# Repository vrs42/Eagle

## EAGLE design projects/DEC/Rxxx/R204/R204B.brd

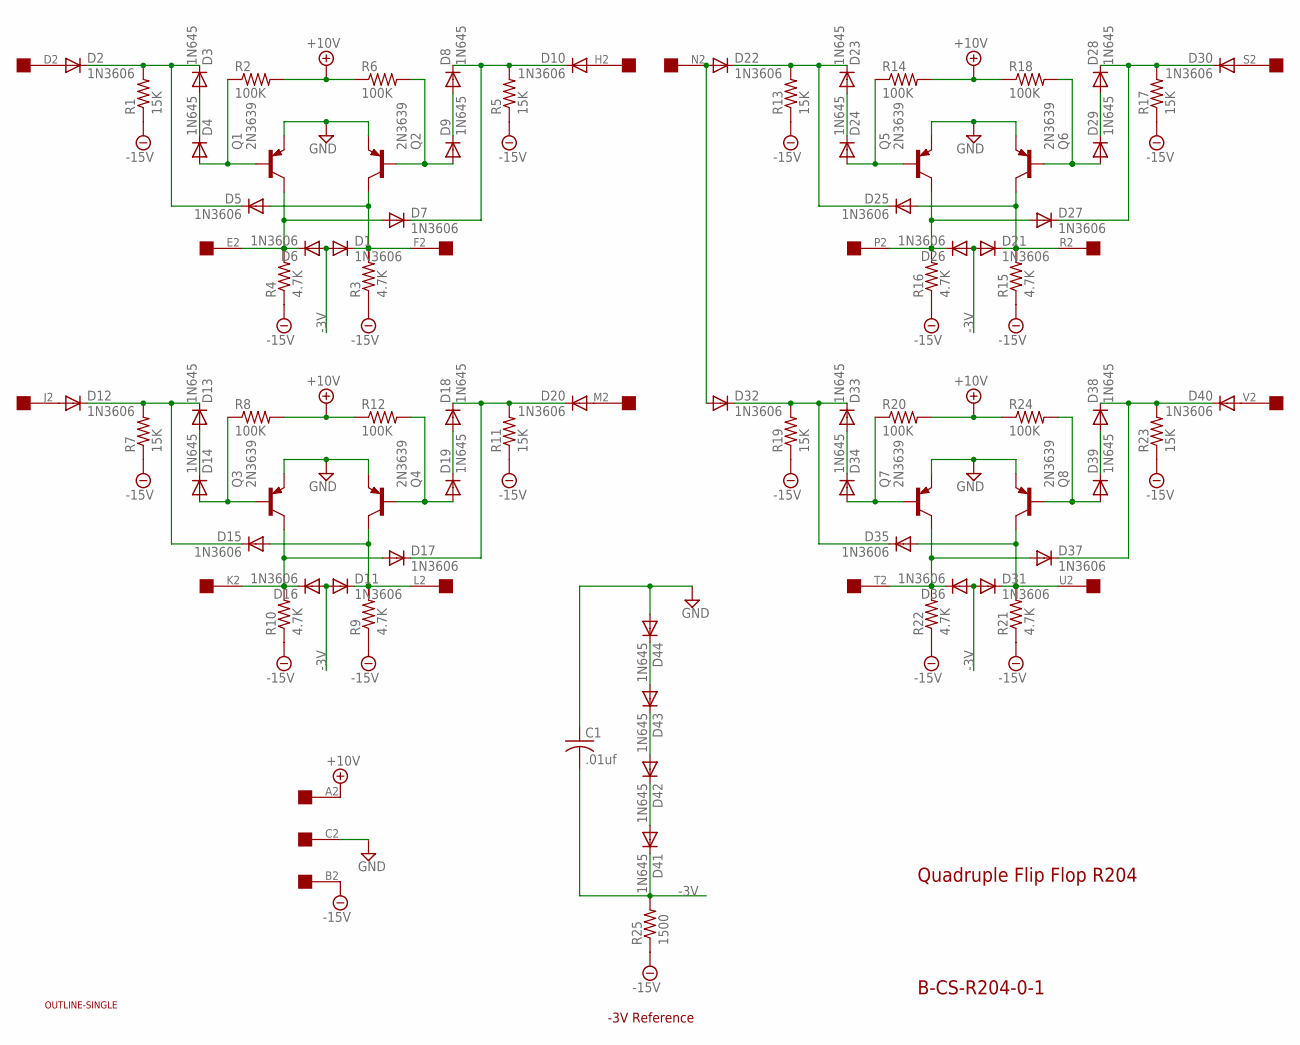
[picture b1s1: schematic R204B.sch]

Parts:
C1: .01uf; C050-025X075
D1, D2, D5, D6, D7, D10, D11, D12, D15, D16, D17, D20, D21, D22, D25, D26, D27, D30, D31, D32, D35, D36, D37, D40: 1N3606; DO35-10
D3, D4, D8, D9, D13, D14, D18, D19, D23, D24, D28, D29, D33, D34, D38, D39, D41, D42, D43, D44: 1N645; DO35-10
Q1, Q2, Q3, Q4, Q5, Q6, Q7, Q8: 2N3639; TO39
R1, R5, R7, R11, R13, R17, R19, R23: 15K; 0207/10
R2, R6, R8, R12, R14, R18, R20, R24: 100K; 0207/10
R3, R4, R9, R10, R15, R16, R21, R22: 4.7K; 0207/10
R25: 1500; 0207/10
U$1: OUTLINE-SINGLE; SINGLE
U$2: EDGE-1; EDGE-CON1

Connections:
+10V: R2.2, R6.1, R8.2, R12.1, R14.2, R18.1, R20.2, R24.1, U$2.A2
-0.8V: D43.A, D44.C
-3V: C1.2, D1.A, D6.A, D11.A, D16.A, D21.A, D26.A, D31.A, D36.A, D41.C, R25.2
-15V: R1.1, R3.1, R4.1, R5.1, R7.1, R9.1, R10.1, R11.1, R13.1, R15.1, R16.1, R17.1, R19.1, R21.1, R22.1, R23.1, R25.1, U$2.B2
E: D6.C, D7.A, Q1.3 (C), R4.2, U$2.E2
F: D1.C, D5.A, Q2.3 (C), R3.2, U$2.F2
GND: C1.1, D44.A, Q1.1 (E), Q2.1 (E), Q3.1 (E), Q4.1 (E), Q5.1 (E), Q6.1 (E), Q7.1 (E), Q8.1 (E), U$2.C2
K: D16.C, D17.A, Q3.3 (C), R10.2, U$2.K2
L: D11.C, D15.A, Q4.3 (C), R9.2, U$2.L2
unnamed: D13.A, D14.C
unnamed: D7.C, D8.C, D10.C, R5.2
unnamed: D12.C, D13.C, D15.C, R7.2
unnamed: D12.A, U$2.J2
unnamed: D14.A, Q3.2 (B), R8.1
unnamed: D8.A, D9.C
unnamed: D10.A, U$2.H2
unnamed: D17.C, D18.C, D20.C, R11.2
unnamed: D2.C, D3.C, D5.C, R1.2
unnamed: D2.A, U$2.D2
unnamed: D18.A, D19.C
unnamed: D20.A, U$2.M2
unnamed: D42.A, D43.C
unnamed: D4.A, Q1.2 (B), R2.1
unnamed: D19.A, Q4.2 (B), R12.2
unnamed: D41.A, D42.C
unnamed: D9.A, Q2.2 (B), R6.2
unnamed: D23.A, D24.C
unnamed: D22.C, D23.C, D25.C, R13.2
unnamed: D22.A, D32.A, U$2.N2
unnamed: D24.A, Q5.2 (B), R14.1
unnamed: D27.C, D28.C, D30.C, R17.2
unnamed: D3.A, D4.C
unnamed: D28.A, D29.C
unnamed: D30.A, U$2.S2
unnamed: D29.A, Q6.2 (B), R18.2
unnamed: D33.A, D34.C
unnamed: D32.C, D33.C, D35.C, R19.2
unnamed: D34.A, Q7.2 (B), R20.1
unnamed: D37.C, D38.C, D40.C, R23.2
unnamed: D38.A, D39.C
unnamed: D40.A, U$2.V2
unnamed: D39.A, Q8.2 (B), R24.2
P: D26.C, D27.A, Q5.3 (C), R16.2, U$2.P2
R: D21.C, D25.A, Q6.3 (C), R15.2, U$2.R2
T: D36.C, D37.A, Q7.3 (C), R22.2, U$2.T2
U: D31.C, D35.A, Q8.3 (C), R21.2, U$2.U2

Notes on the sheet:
Quadruple Flip Flop R204
B-CS-R204-0-1
-3V Reference

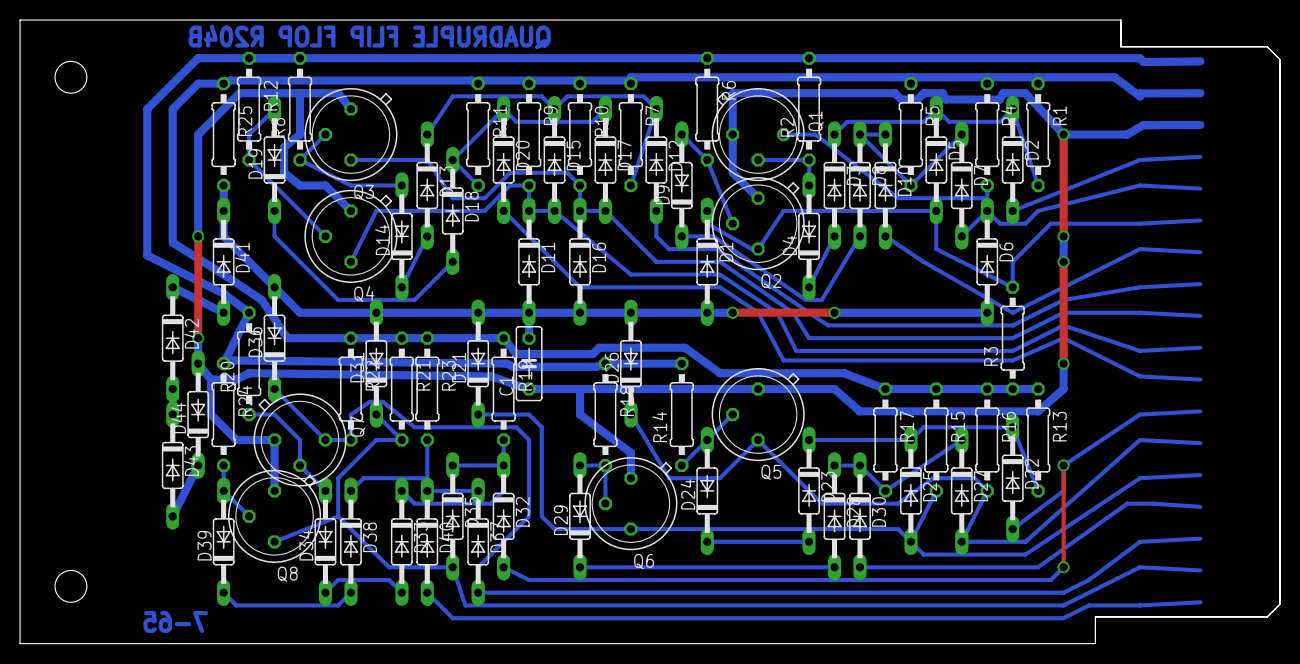
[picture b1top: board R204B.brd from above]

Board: 2 copper layers, 125.7 x 62.2 mm, 80 parts (0 on the bottom side), 46 nets.

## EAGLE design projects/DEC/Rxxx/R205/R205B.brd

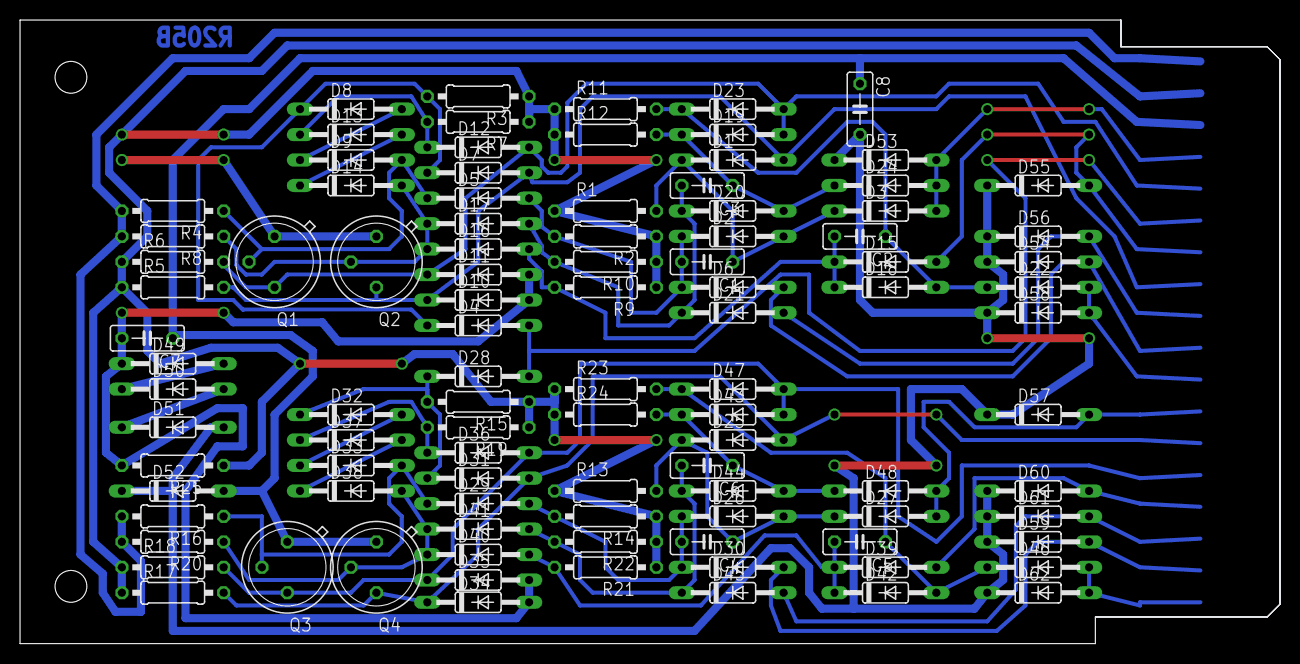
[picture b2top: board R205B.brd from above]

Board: 2 copper layers, 125.7 x 62.2 mm, 101 parts (0 on the bottom side), 46 nets.

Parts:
C1, C2, C3, C4, C5, C6: 100pf 5%; C050-025X075
C7, C8: .01uf; C050-025X075
D1, D2, D3, D4, D5, D6, D7, D10, D11, D12, D15, D16, D17, D18, D19, D20, D21, D22, D23, D24, D25, D26, D27, D28, D29, D30, D31, D34, D35, D36, D39, D40, D41, D42, D43, D44, D45, D46, D47, D48, D53, D54, D55, D56, D57, D58, D59, D60, D61, D62: 1N3606; DO35-10
D8, D9, D13, D14, D32, D33, D37, D38, D49, D50, D51, D52: 1N645; DO35-10
Q1, Q2, Q3, Q4: 2N3639; TO39
R1, R2, R3, R7, R9, R10, R11, R12, R13, R14, R15, R19, R21, R22, R23, R24: 15K; 0207/10
R4, R8, R16, R20: 100K; 0207/10
R5, R6, R17, R18: 4.7K; 0207/10
R25: 1500; 0207/10
U$1: OUTLINE-SINGLE; SINGLE
U$2: EDGE-1; EDGE-CON1

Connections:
+10V: R4.2, R8.2, R16.2, R20.2, U$2.A2
-0.8V: C8.2, D51.A, D52.C, D53.C, D54.C, D55.C, D56.C, D57.C, D58.C, D59.C, D60.C, D61.C, D62.C
-3V: C7.2, D10.A, D11.A, D34.A, D35.A, D49.C, R25.2
-15V: R1.1, R2.1, R3.1, R5.1, R6.1, R7.1, R9.1, R10.1, R11.1, R12.1, R13.1, R14.1, R15.1, R17.1, R18.1, R19.1, R21.1, R22.1, R23.1, R24.1, R25.1, U$2.B2
E: D11.C, D12.A, D19.A, D23.A, Q1.3, R6.2, U$2.E2
GND: C7.1, C8.1, D52.A, Q1.1, Q2.1, Q3.1, Q4.1, U$2.C2
J: D1.A, D7.A, D10.C, Q2.3, R5.2, U$2.J2
unnamed: C4.1, D25.C, D26.A, D27.C, R13.2
unnamed: C3.1, D19.C, D20.A, D24.C, R12.2
unnamed: C1.2, D2.C, D5.A, D6.C, R2.2
unnamed: D3.A, D24.A, D53.A, U$2.D2
unnamed: D6.A, D54.A, U$2.L2
unnamed: D13.A, D14.C
unnamed: D32.A, D33.C
unnamed: C3.2, D17.A, D20.C, D21.C, R10.2
unnamed: D4.C, D7.C, D8.C, R3.2
unnamed: D4.A, D28.A, U$2.F2
unnamed: D21.A, D56.A, U$2.K2
unnamed: D12.C, D13.C, R7.2
unnamed: D50.A, D51.C
unnamed: D5.C, D9.A, Q1.2, R4.1
unnamed: C4.2, D26.C, D29.A, D30.C, R14.2
unnamed: D49.A, D50.C
unnamed: D14.A, D16.C, D17.C, Q2.2, R8.1
unnamed: D30.A, D59.A, U$2.U2
unnamed: D28.C, D31.C, D32.C, R15.2
unnamed: D29.C, D33.A, Q3.2, R16.1
unnamed: C1.1, D1.C, D2.A, D3.C, R1.2
unnamed: D8.A, D9.C
unnamed: C6.1, D43.C, D44.A, D48.C, R24.2
unnamed: D37.A, D38.C
unnamed: C6.2, D41.A, D44.C, D45.C, R22.2
unnamed: D45.A, D61.A, U$2.T2
unnamed: C2.1, D18.A, D22.C, D23.C, R11.2
unnamed: D38.A, D40.C, D41.C, Q4.2, R20.1
unnamed: D22.A, D58.A, U$2.M2
unnamed: C2.2, D15.C, D16.A, D18.C, R9.2
unnamed: D15.A, D55.A, U$2.H2
unnamed: D36.C, D37.C, R19.2
unnamed: C5.1, D42.A, D46.C, D47.C, R23.2
unnamed: D46.A, D62.A, U$2.V2
unnamed: C5.2, D39.C, D40.A, D42.C, R21.2
unnamed: D39.A, D60.A, U$2.S2
unnamed: D27.A, D48.A, D57.A, U$2.N2
P: D25.A, D31.A, D34.C, Q4.3, R17.2, U$2.P2
R: D35.C, D36.A, D43.A, D47.A, Q3.3, R18.2, U$2.R2

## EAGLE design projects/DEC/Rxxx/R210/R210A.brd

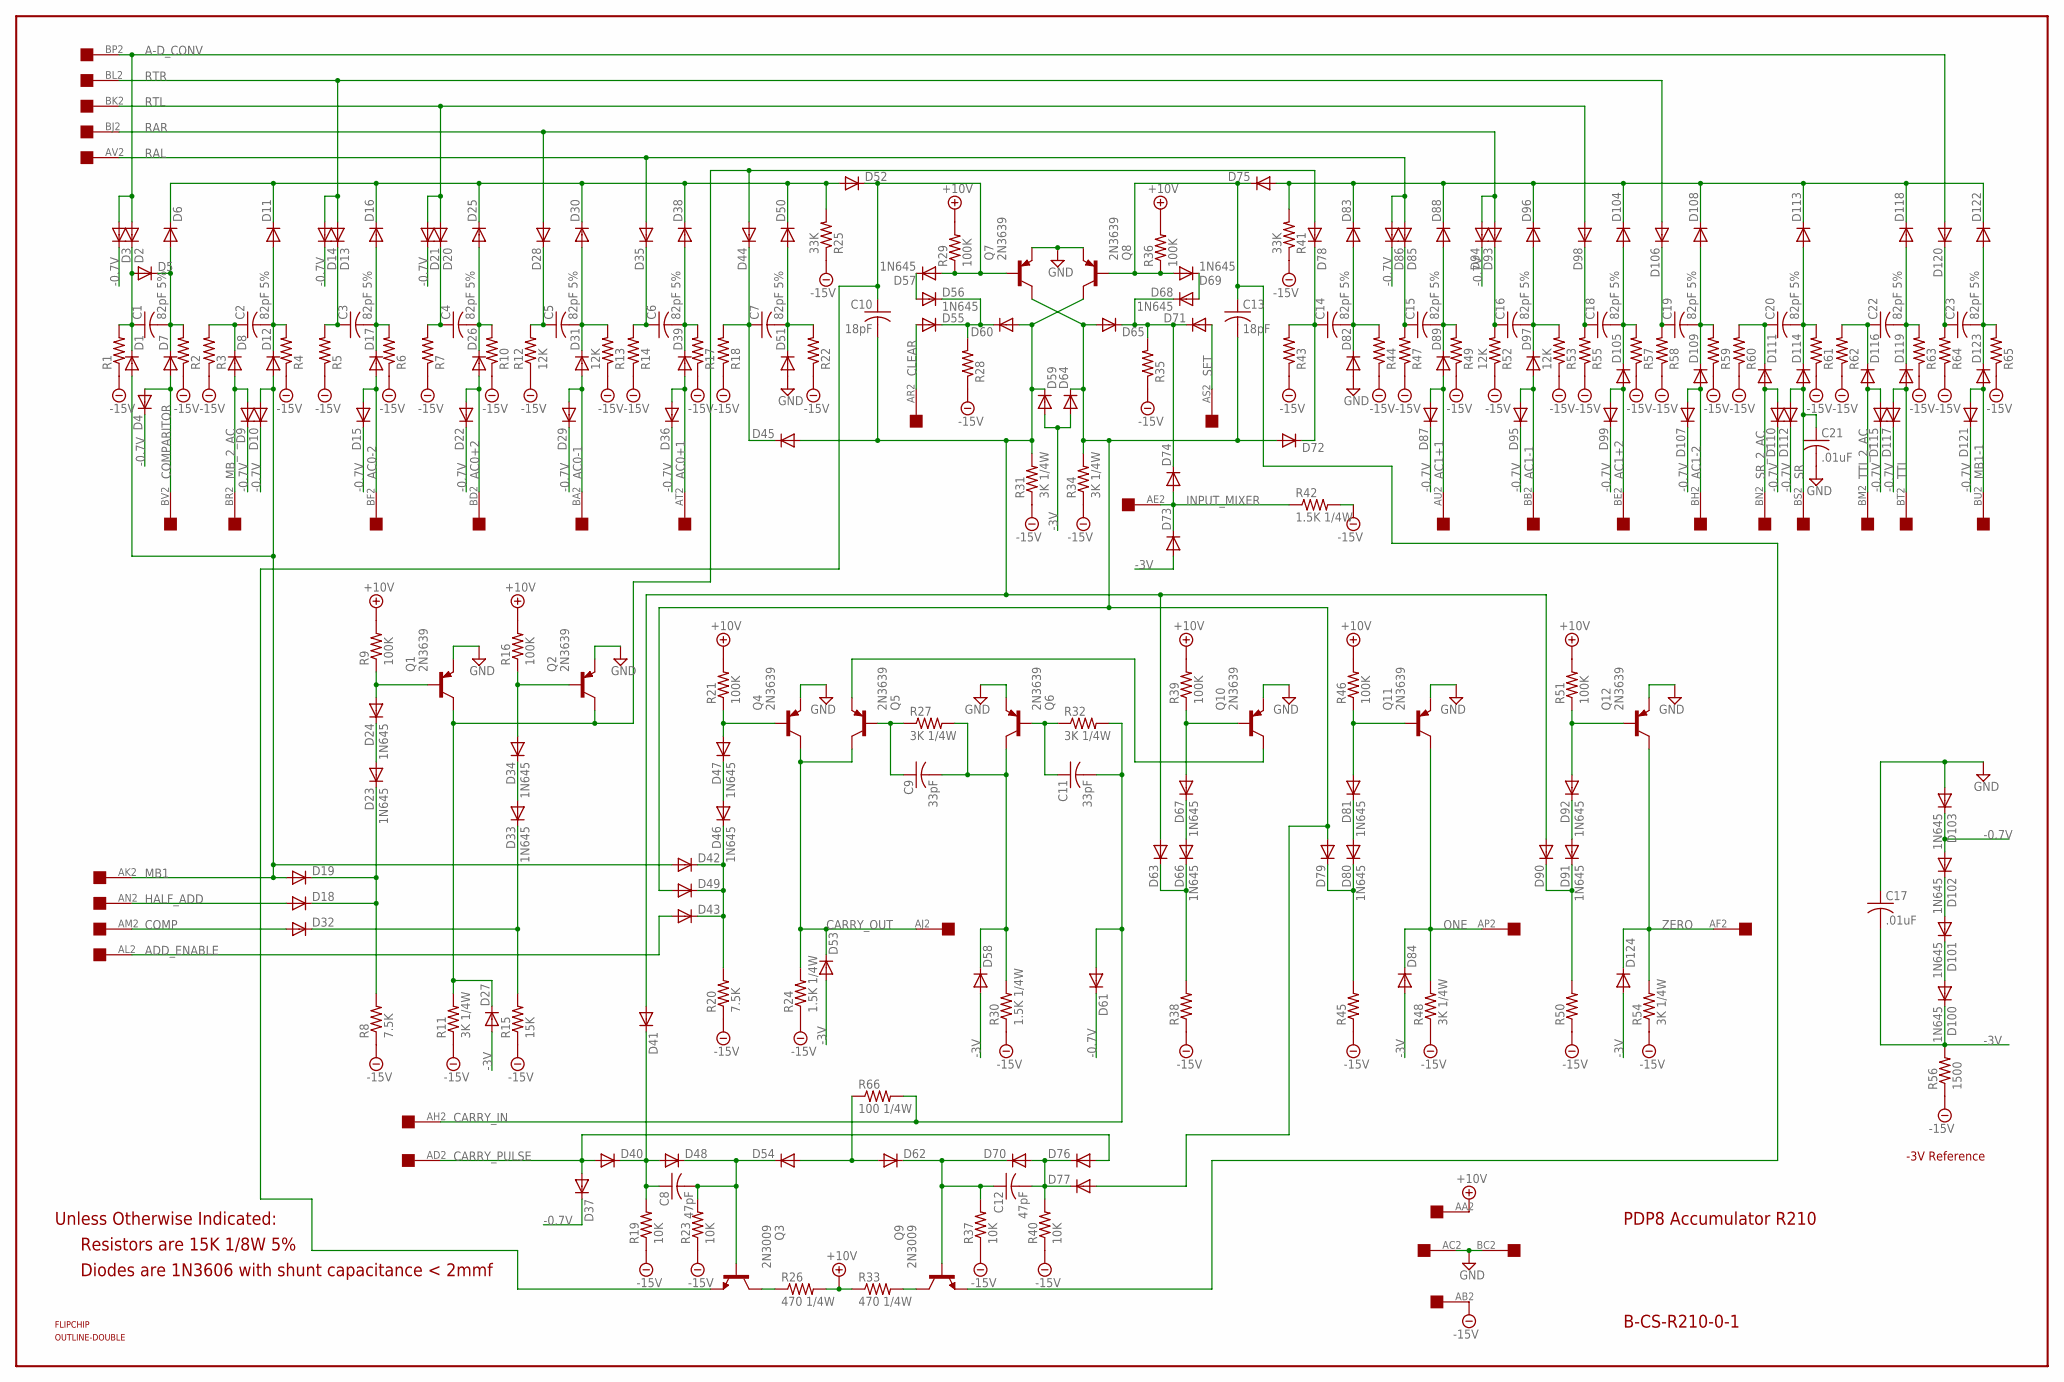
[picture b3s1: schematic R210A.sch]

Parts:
C1, C2, C3, C4, C5, C6, C7, C14, C15, C16, C18, C19, C20, C22, C23: 82pF 5%; C075-032X103
C8, C12: 47pF; C075-032X103
C9, C11: 33pF; C075-032X103
C10, C13: 18pF; C075-032X103
C17, C21: .01uF; C050-025X075
D1, D2, D3, D4, D5, D6, D7, D8, D9, D10, D11, D12, D13, D14, D15, D16, D17, D18, D19, D20, D21, D22, D25, D26, D27, D28, D29, D30, D31, D32, D35, D36, D37, D38, D39, D40, D41, D42, D43, D44, D45, D48, D49, D50, D51, D52, D53, D54, D55, D58, D59, D60, D61, D62, D63, D64, D65, D70, D71, D72, D73, D74, D75, D76, D77, D78, D79, D82, D83, D84, D85, D86, D87, D88, D89, D90, D93, D94, D95, D96, D97, D98, D99, D104, D105, D106, D107, D108, D109, D110, D111, D112, D113, D114, D115, D116, D117, D118, D119, D120, D121, D122, D123, D124: 1N4148DO35-10; DO35-10
D23, D24, D33, D34, D46, D47, D56, D57, D66, D67, D68, D69, D80, D81, D91, D92, D100, D101, D102, D103: 1N645; DO35-10
Q1, Q2, Q4, Q5, Q6, Q7, Q8, Q10, Q11, Q12: 2N3639; TO39
Q3, Q9: 2N3009; TO5
R1, R2, R3, R4, R5, R6, R7, R10, R14, R17, R18, R22, R28, R35, R38, R43, R44, R45, R47, R49, R50, R55, R57, R58, R59, R60, R61, R62, R63, R64, R65: R-US_0207/10; 0207/10
R8, R20: 7.5K; 0207/10
R9, R16, R21, R29, R36, R39, R46, R51: 100K; 0207/10
R11, R27, R31, R32, R34, R48, R54: 3K 1/4W; 0207/10
R12, R13, R52, R53: 12K; 0207/10
R15: 15K; 0207/10
R19, R23, R37, R40: 10K; 0207/10
R24, R30, R42: 1.5K 1/4W; 0207/10
R25, R41: 33K; 0207/10
R26, R33: 470 1/4W; 0207/10
R56: 1500; 0207/10
R66: 100 1/4W; 0207/10
U$1: DOUBLE; EDGE-CON4
U$2: FLIPCHIP
U$3: OUTLINE-DOUBLE; DOUBLE

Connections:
+10V: R9.2, R16.2, R21.2, R26.2, R29.2, R33.1, R36.2, R39.2, R46.2, R51.2, U$1.AA2
-0.7V: D3.C, D4.C, D9.C, D10.C, D14.C, D15.C, D21.C, D22.C, D29.C, D36.C, D37.C, D61.C, D86.C, D87.C, D94.C, D95.C, D99.C, D102.A, D103.C, D107.C, D110.C, D112.C, D115.C, D117.C, D121.C
-3V: C17.2, D27.A, D53.A, D58.A, D59.A, D64.A, D73.A, D84.A, D100.C, D124.A, R56.2
-15V: R1.1, R2.1, R3.1, R4.1, R5.1, R6.1, R7.1, R8.1, R10.1, R11.1, R12.1, R13.1, R14.1, R15.1, R17.1, R18.1, R19.1, R20.1, R22.1, R23.1, R24.1, R25.1, R28.1, R30.1, R31.1, R34.1, R35.1, R37.1, R38.1, R40.1, R41.1, R42.2, R43.1, R44.1, R45.1, R47.1, R48.1, R49.1, R50.1, R52.1, R53.1, R54.1, R55.1, R56.1, R57.1, R58.1, R59.1, R60.1, R61.1, R62.1, R63.1, R64.1, R65.1, U$1.AB2
A-D_CONV: D2.A, D3.A, D120.A, U$1.BP2
AC0+1: D36.A, D39.A, U$1.AT2
AC0+2: D22.A, D26.A, U$1.BD2
AC0-1: D29.A, D31.A, U$1.BA2
AC0-2: D15.A, D17.A, U$1.BF2
AC1+1: D87.A, D89.A, U$1.AU2
AC1+2: D99.A, D105.A, U$1.BE2
AC1-1: D95.A, D97.A, U$1.BB2
AC1-2: D107.A, D109.A, U$1.BH2
ADD_ENABLE: D43.A, U$1.AL2
CARRY_IN: C11.2, D61.A, R32.2, R66.2, U$1.AH2
CARRY_OUT: D53.C, Q4.3 (C), Q5.3 (C), R24.2, U$1.AJ2
CARRY_PULSE: D37.A, D40.A, D76.A, U$1.AD2
CLEAR: D55.A, U$1.AR2
COMP: D32.A, U$1.AM2
COMPARITOR: D4.A, D7.A, U$1.BV2
GND: C17.1, C21.2, D51.A, D82.A, D103.A, Q1.1 (E), Q2.1 (E), Q4.1 (E), Q6.1 (E), Q7.1 (E), Q8.1 (E), Q10.1 (E), Q11.1 (E), Q12.1 (E), U$1.AC2, U$1.BC2
HALF_ADD: D18.A, U$1.AN2
INPUT_MIXER: D73.C, D74.A, R42.1, U$1.AE2
MB1: D1.A, D10.A, D12.A, D19.A, D42.A, U$1.AK2
MB1-1: D121.A, D123.A, U$1.BU2
MB_2_AC: D8.A, D9.A, U$1.BR2
unnamed: D6.C, D11.C, D16.C, D25.C, D30.C, D38.C, D50.C, D52.A, R25.2
unnamed: D27.C, D44.A, D78.A, Q1.3 (C), Q2.3 (C), R11.2
unnamed: C1.2, D5.C, D6.A, D7.C, R2.2
unnamed: C1.1, D1.C, D2.C, D5.A, R1.2
unnamed: D18.C, D19.C, D23.C, R8.2
unnamed: C2.1, D8.C, R3.2
unnamed: C2.2, D11.A, D12.C, R4.2
unnamed: C10.2, D41.A, D45.A, D59.C, D60.A, D63.A, D90.A, Q8.3 (C), R31.2
unnamed: C13.2, D49.A, D64.C, D65.A, D72.A, D77.A, D79.A, Q7.3 (C), R34.2
unnamed: D55.C, D56.C, D60.C, R28.2
unnamed: D56.A, D57.C
unnamed: C3.1, D13.C, R5.2
unnamed: D101.A, D102.C
unnamed: C3.2, D16.A, D17.C, R6.2
unnamed: C10.1, D52.C, D57.A, Q3.1 (E), Q7.2 (B), R29.1
unnamed: D100.A, D101.C
unnamed: D66.A, D67.C
unnamed: C4.1, D20.C, R7.2
unnamed: C4.2, D25.A, D26.C, R10.2
unnamed: C13.1, D69.A, D75.C, Q8.2 (B), Q9.1 (E), R36.1
unnamed: D68.A, D69.C
unnamed: C5.1, D28.C, R12.2
unnamed: C5.2, D30.A, D31.C, R13.2
unnamed: D65.C, D68.C, D71.C, D74.C, R35.2
unnamed: D75.A, D83.C, D88.C, D96.C, D104.C, D108.C, D113.C, D118.C, D122.C, R41.2
unnamed: C6.1, D35.C, R14.2
unnamed: C6.2, D38.A, D39.C, R17.2
unnamed: C12.1, D62.C, D70.C, Q9.2 (B), R37.2
unnamed: C14.1, D72.C, D78.C, R43.2
unnamed: C7.1, D44.C, D45.C, R18.2
unnamed: C7.2, D50.A, D51.C, R22.2
unnamed: C14.2, D82.C, D83.A, R44.2
unnamed: C15.1, D85.C, R47.2
unnamed: C15.2, D88.A, D89.C, R49.2
unnamed: C16.1, D93.C, R52.2
unnamed: C16.2, D96.A, D97.C, R53.2
unnamed: C18.1, D98.C, R55.2
unnamed: C18.2, D104.A, D105.C, R57.2
unnamed: D24.A, Q1.2 (B), R9.1
unnamed: D23.A, D24.C
unnamed: C19.1, D106.C, R58.2
unnamed: C19.2, D108.A, D109.C, R59.2
unnamed: D33.A, D34.C
unnamed: C20.1, D111.C, R60.2
unnamed: C20.2, D113.A, D114.C, R61.2
unnamed: C12.2, D70.A, D76.C, D77.C, R40.2
unnamed: D32.C, D33.C, R15.2
unnamed: C22.1, D116.C, R62.2
unnamed: C22.2, D118.A, D119.C, R63.2
unnamed: D34.A, Q2.2 (B), R16.1
unnamed: D47.A, Q4.2 (B), R21.1
unnamed: C23.1, D120.C, R64.2
unnamed: C23.2, D122.A, D123.C, R65.2
unnamed: D46.A, D47.C
unnamed: D42.C, D43.C, D46.C, D49.C, R20.2
unnamed: C9.1, Q5.2 (B), R27.1
unnamed: C9.2, D58.C, Q6.3 (C), R27.2, R30.2
unnamed: Q5.1 (E), Q10.3 (C)
unnamed: C11.1, Q6.2 (B), R32.1
unnamed: D54.A, D62.A, R66.1
unnamed: D67.A, Q10.2 (B), R39.1
unnamed: D63.C, D66.C, R38.2
unnamed: D81.A, Q11.2 (B), R46.1
unnamed: C8.1, D40.C, D41.C, D48.A, R19.2
unnamed: D80.A, D81.C
unnamed: D79.C, D80.C, R45.2
unnamed: D92.A, Q12.2 (B), R51.1
unnamed: D90.C, D91.C, R50.2
unnamed: D91.A, D92.C
unnamed: C8.2, D48.C, D54.C, Q3.2 (B), R23.2
unnamed: Q3.3 (C), R26.1
unnamed: Q9.3 (C), R33.2
ONE: D84.C, Q11.3 (C), R48.2, U$1.AP2
RAL: D35.A, D85.A, D86.A, U$1.AV2
RAR: D28.A, D93.A, D94.A, U$1.BJ2
RTL: D20.A, D21.A, D98.A, U$1.BK2
RTR: D13.A, D14.A, D106.A, U$1.BL2
SET: D71.A, U$1.AS2
SR: C21.1, D112.A, D114.A, U$1.BS2
SR_2_AC: D110.A, D111.A, U$1.BN2
TTI: D117.A, D119.A, U$1.BT2
TTI_2_AC: D115.A, D116.A, U$1.BM2
ZERO: D124.C, Q12.3 (C), R54.2, U$1.AF2

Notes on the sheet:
PDP8 Accumulator R210
B-CS-R210-0-1
-3V Reference
Resistors are 15K 1/8W 5%
Diodes are 1N3606 with shunt capacitance < 2mmf
Unless Otherwise Indicated:

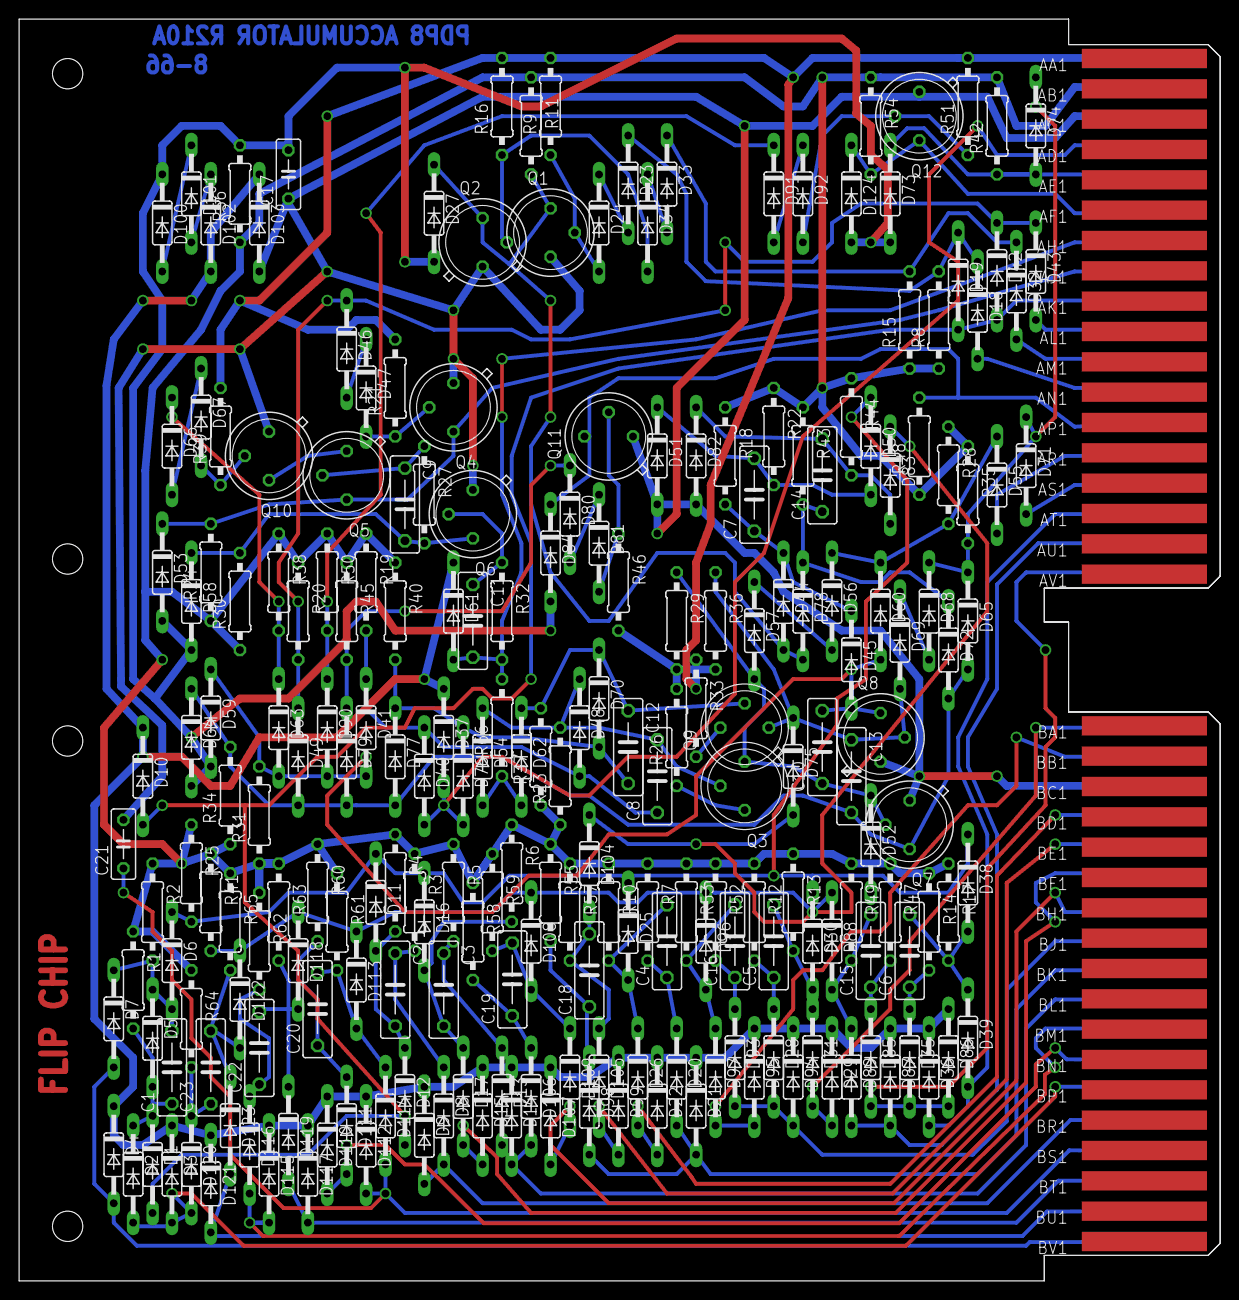
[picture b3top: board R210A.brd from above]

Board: 2 copper layers, 125.7 x 132.1 mm, 228 parts (0 on the bottom side), 109 nets.
